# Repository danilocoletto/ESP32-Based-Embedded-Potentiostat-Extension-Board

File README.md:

# ESP32-Based Real-Time Embedded Potentiostat Extension Board

> **⚠️ PROJECT STATUS: ONGOING**
> This project is currently under active development. The hardware design and firmware are subject to changes. Please check the `dev` branch for the latest updates.

## Key Features

- Real-time embedded architecture using **ESP32 + FreeRTOS**
- **24-bit precision ADC (ADS1255)** for nanoampere current measurements
- **16-bit DAC waveform generation** for electrochemical techniques
- Modular **analog front-end (AFE)** design
- Designed for **voltammetry and amperometry**
- **KiCad open hardware design**
- Firmware based on **ESP-IDF**

## 📖 Introduction

This repository contains the open-source hardware and firmware for a **Real-Time Embedded Potentiostat**. Designed as a high-precision **modular extension board**, this instrument allows for advanced electrochemical analysis (Voltammetry, Amperometry) in field applications.

A defining feature of this design is its **controller-agnostic modularity**. The board functions as a dedicated analog "backpack," decoupling the sensitive electrochemical front-end from the digital control logic. This architecture allows the board to be driven by various devices depending on the application needs:

* **ESP32 Implementation (Current Focus):** The primary implementation utilizes an **ESP32** microcontroller. This was chosen to provide **hard real-time execution** via FreeRTOS and to enable **wireless connectivity** (Wi-Fi/Bluetooth) for remote field monitoring in the future development.
* **External Instrumentation:** The header layout and signal routing were specifically designed to allow direct interfacing with test equipment such as the **Analog Discovery 2** (or similar oscilloscopes/logic analyzers). This allows user flexibility to to have alternative control strategies such as an ESP32, ATMEGA, STM32 or even an Analog Discovery.

### 💡 The Evolution: From Single-Board Computer to Real-Time Embedded
This project represents the **second generation** of the "All-in-One" potentiostat concept.

* **Previous Design (Generation 1):** Based on a **Raspberry Pi 3B+**. While it successfully integrated the user interface and control logic, the reliance on a non-real-time Operating System (Linux) introduced latency challenges for high-speed techniques. The usage of the ADS1110 (240 SPS) also limited the sweep speed.
* **Current Design (Generation 2):** Transitions to an **Embedded Real-Time Architecture**.
    * **Why?** To achieve **deterministic timing** and modular flexibility.
    * **Improvements:** Modular hardware design suitable for extension, significantly lower power consumption, reduced noise floor (nanoampere-level), and the ability to perform fast electrochemical screening without a heavy OS overhead.

## 🛠️ Hardware & Components

The hardware is designed to support nanoampere-level current measurements with a robust analog front-end.
- **KiCad PCB design**
- **MCU:** **ESP32-WROOM/WROVER** (Dual-core, 240 MHz). Handles waveform generation (DAC control), data acquisition (ADC readings), and wireless communication.
- **Analog Front-End (TIA + Control Amplifier):**
    - Improved topology using **High-Precision Rail-to-Rail OpAmps** (e.g., LMP770x Series and LM7721) for the Transimpedance Amplifier (TIA) and Control Amplifier.
    - **MAX4737:** Low-voltage, low on-resistance (RON), quad single-pole/single throw (SPST) analog switches.
    - **MAX4617:** High-Speed, Low-Voltage, CMOS Analog Multiplexers/Switches
- **ADS1255**: 24-bit ADC High-Speed ADC (replacing the slower ADS1110 of the previous version for an ADS1255) to support faster sweep rates (>1000 mV/s) and filter line noise at low current measurements.
- **MAX5217**: 16-bit DAC Low-Power with I2C/SPI interface for precise potential steps.
- **Power Management:** On-board LDOs and precision voltage references (2.500V / 5.000V) to ensure stable operation in field conditions.
- **Anti-Aliasing:** Active 4th-order Sallen-Key filtering to smooth signal steps and reduce noise.

## Firmware

- **ESP-IDF framework**
- **FreeRTOS tasks**
- **SPI driver for ADS1255**
- **I2C driver for DAC**
- **State machine for system management**
- **Baremetal libraries for precise timing during experiments**

## 📂 Repository Structure

The repository is organized as follows:

```
├── Diseno_3D/                          # Fusion360 project and .stl files for 3D case design
├── Hardware/                           # KiCad project files (Schematics, PCB Layout, BOM)
├── Images&Schematics/
│   ├── Images/
│   ├── Interface/
│   ├── Renders/
│   ├── Schematics/
├── Software/ 
│   ├── ESP32_Firmware/ 
│   │   ├── PotentiostatV2_Firmware/    # ESP-IDF C/C++ source code
│   │   │   ├── main/                   # Core logic (FreeRTOS tasks, State Machine)
│   │   │   ├── components/             # Drivers for DAC, ADC, and Potentiostat control
│   │   ├── Main/                       # GUI and Python Backend modules
│   │   │   ├── modules/                # Python backend modules
│   │   │   ├── logos/                  # logos folder
│   │   │   ├── gui/                    # Graphic User Interface .ui file
├── Información/                        # Datasheets and design notes
└── README.md                           # This file
```

## 🔌 Pinout & Interface

*> **Note:** As the PCB layout is being finalized, please refer to the schematic in the `Hardware` folder for the most up-to-date netlist. Below is the current configuration for the ESP32 implementation.*

### ⚡ Analog Front-End Connections
* **WE (Working Electrode):** Input for current measurement.
* **RE (Reference Electrode):** Feedback input (Shielded).
* **CE (Counter Electrode):** Current injection output.

### 🧩 ESP32 GPIO Mapping

| Component | Function | ESP32 GPIO | Description |
| :--- | :--- | :--- | :--- |
| **ADS1255 (ADC)** | **MISO** (DOUT) | **19** | SPI Data Input |
| | **MOSI** (DIN) | **23** | SPI Data Output |
| | **SCLK** | **18** | SPI Clock |
| | **CS** | **5** | Chip Select |
| | **DRDY** | **4** | Data Ready Interrupt |
| | **CLOCK** | **16** | (Optional) ADS1255 System Clock |
| **MAX5217 (DAC)** | **SDA** | **21** | I2C Data |
| | **SCL** | **22** | I2C Clock |
| | **NAUX** | **32** | Aux/Load Control |
| **MAX4617 (Mux)** | **SEL A** | **27** | Range/Gain Select Bit A |
| | **SEL B** | **26** | Range/Gain Select Bit B |
| | **SEL C** | **25** | Range/Gain Select Bit C |
| **MAX4737 (Switches)**| **CR SHORT EN**| **14** | Counter-Reference Short Enable |
| | **RE FB EN** | **33** | Reference Feedback Enable |
| | **WE EN** | **13** | Working Electrode Enable |
| | **CE EN** | **15** | Counter Electrode Enable |
| **Misc** | **GREEN LED** | **2** | Onboard Status LED (Green) |

## 📚 References & Context

For context on the theoretical background and the first generation of this device, please refer to our published article on the Raspberry Pi-based version:

> **(All-in-One) Open Source Potentiostat for Field Analysis Based on Raspberry Pi**
> *Hardware* 2024, 3(4), 17; [https://doi.org/10.3390/hardware3040017](https://www.mdpi.com/2813-6640/3/4/17)

Case Design:

> *3D Printed Design by [Boris Diaduch](https://www.linkedin.com/in/borisdiaduch/)*

---

*Maintained by [Ing. Danilo Coletto Gallego](www.linkedin.com/in/danilocoletto)*

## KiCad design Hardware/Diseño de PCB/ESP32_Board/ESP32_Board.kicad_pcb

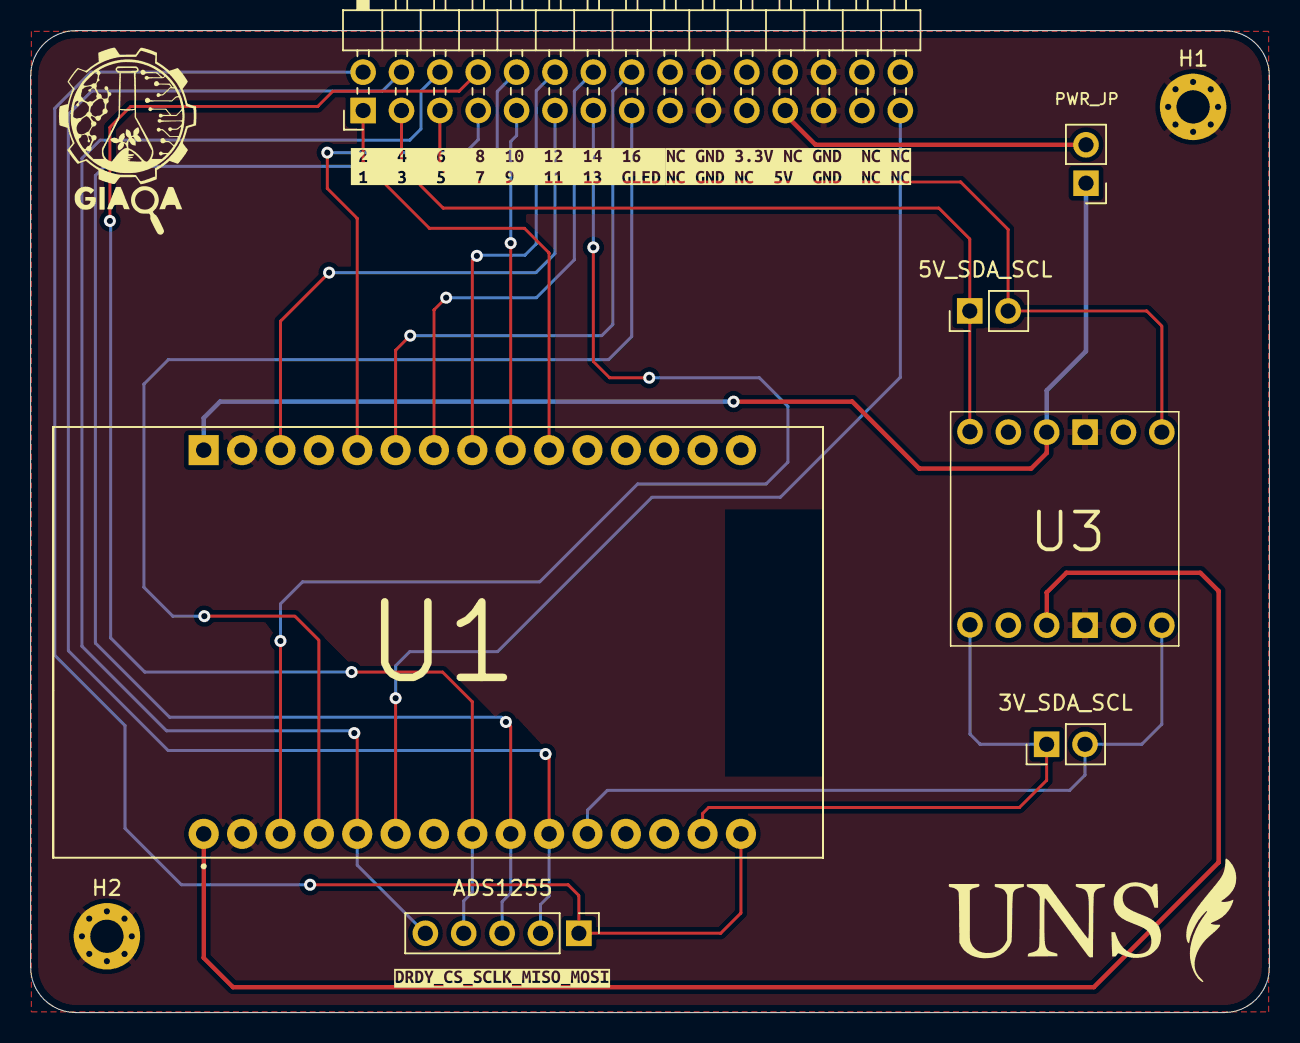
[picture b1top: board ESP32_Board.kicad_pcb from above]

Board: 2 copper layers, 82.0 x 65.0 mm, 13 parts (0 on the bottom side), 23 nets.

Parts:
3V_SDA_SCL, 5V_SDA_SCL: Conn_01x02; PinHeader_1x02_P2.54mm_Vertical
ADS1255: Conn_01x05; PinHeader_1x05_P2.54mm_Vertical
H1, H2: MountingHole_Pad; MountingHole_2.2mm_M2_Pad_Via
J1: Conn_02x15_Odd_Even; PinHeader_2x15_P2.54mm_Horizontal
PWR_JP: Jumper_2_Open; PinHeader_1x02_P2.54mm_Vertical
U1: ESP32 - DEVKIT; MODULE_ESP32_DEVKIT_V1_CORRECTED
U2: logo; logo_uns
U3: LevelShifter
kibuzzard-69A1DE73: G***; kibuzzard-69A1DE73
kibuzzard-69A5AE09: G***; kibuzzard-69A5AE09
kibuzzard-69C42740: G***; kibuzzard-69C42740

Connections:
+3.3V: U1.2 (3V3), U3.3 (3.3V)
+5V: PWR_JP.1 (A), U1.0 (VIN), U3.10 (5V)
/5V: J1.23, PWR_JP.2 (B)
/ADS1255_CLOCK_PIN: J1.29, U1.27 (RX2/D16)
/ADS1255_CS: ADS1255.4, J1.8, U1.29 (D5)
/ADS1255_DIN_MOSI: ADS1255.1, J1.2, U1.37 (D23)
/ADS1255_DOUT_MISO: ADS1255.2, J1.4, U1.31 (D19)
/ADS1255_DRDY: ADS1255.5, J1.6, U1.26 (D4)
/ADS1255_SCLK: ADS1255.3, J1.10, U1.30 (D18)
/GREEN_LED: J1.15, U1.24 (D2)
/MAX4617_SEL_A: J1.16, U1.12 (D27)
/MAX4617_SEL_B: J1.14, U1.11 (D26)
/MAX4617_SEL_C: J1.12, U1.10 (D25)
/MAX4737_CE_EN: J1.13, U1.23 (D15)
/MAX4737_CR_SHORT_EN: J1.7, U1.13 (D14)
/MAX4737_RE_FB_EN: J1.9, U1.9 (D33)
/MAX4737_WE_EN: J1.11, U1.16 (D13)
/MAX_5217_NAUX: J1.1, U1.8 (D32)
/MAX_5217_SCL: 3V_SDA_SCL.1, U1.36 (D22), U3.1 (TXI1)
/MAX_5217_SDA: 3V_SDA_SCL.2, U1.33 (D21), U3.6 (TXI2)
/TO_DAC_SCL_PIN_3: 5V_SDA_SCL.1, J1.3, U3.12 (TXD1)
/TO_DAC_SDA_PIN_5: 5V_SDA_SCL.2, J1.5, U3.7 (TXD2)
GND: H1.1, H2.1, J1.19, J1.20, J1.25, J1.26, U1.1 (GND), U1.38 (GND), U3.4 (GND), U3.9 (GND)

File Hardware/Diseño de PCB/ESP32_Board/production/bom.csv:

Designator,Footprint,Quantity,Value,LCSC Part #
"3V_SDA_SCL, 5V_SDA_SCL",PinHeader_1x02_P2.54mm_Vertical,2,Conn_01x02,
ADS1255,PinHeader_1x05_P2.54mm_Vertical,1,Conn_01x05,
J1,PinHeader_2x15_P2.54mm_Horizontal,1,Conn_02x15_Odd_Even,
PWR_JP,PinHeader_1x02_P2.54mm_Vertical,1,Jumper_2_Open,
U1,MODULE_ESP32_DEVKIT_V1_CORRECTED,1,ESP32 - DEVKIT,
U3,LevelShifter,1,~,

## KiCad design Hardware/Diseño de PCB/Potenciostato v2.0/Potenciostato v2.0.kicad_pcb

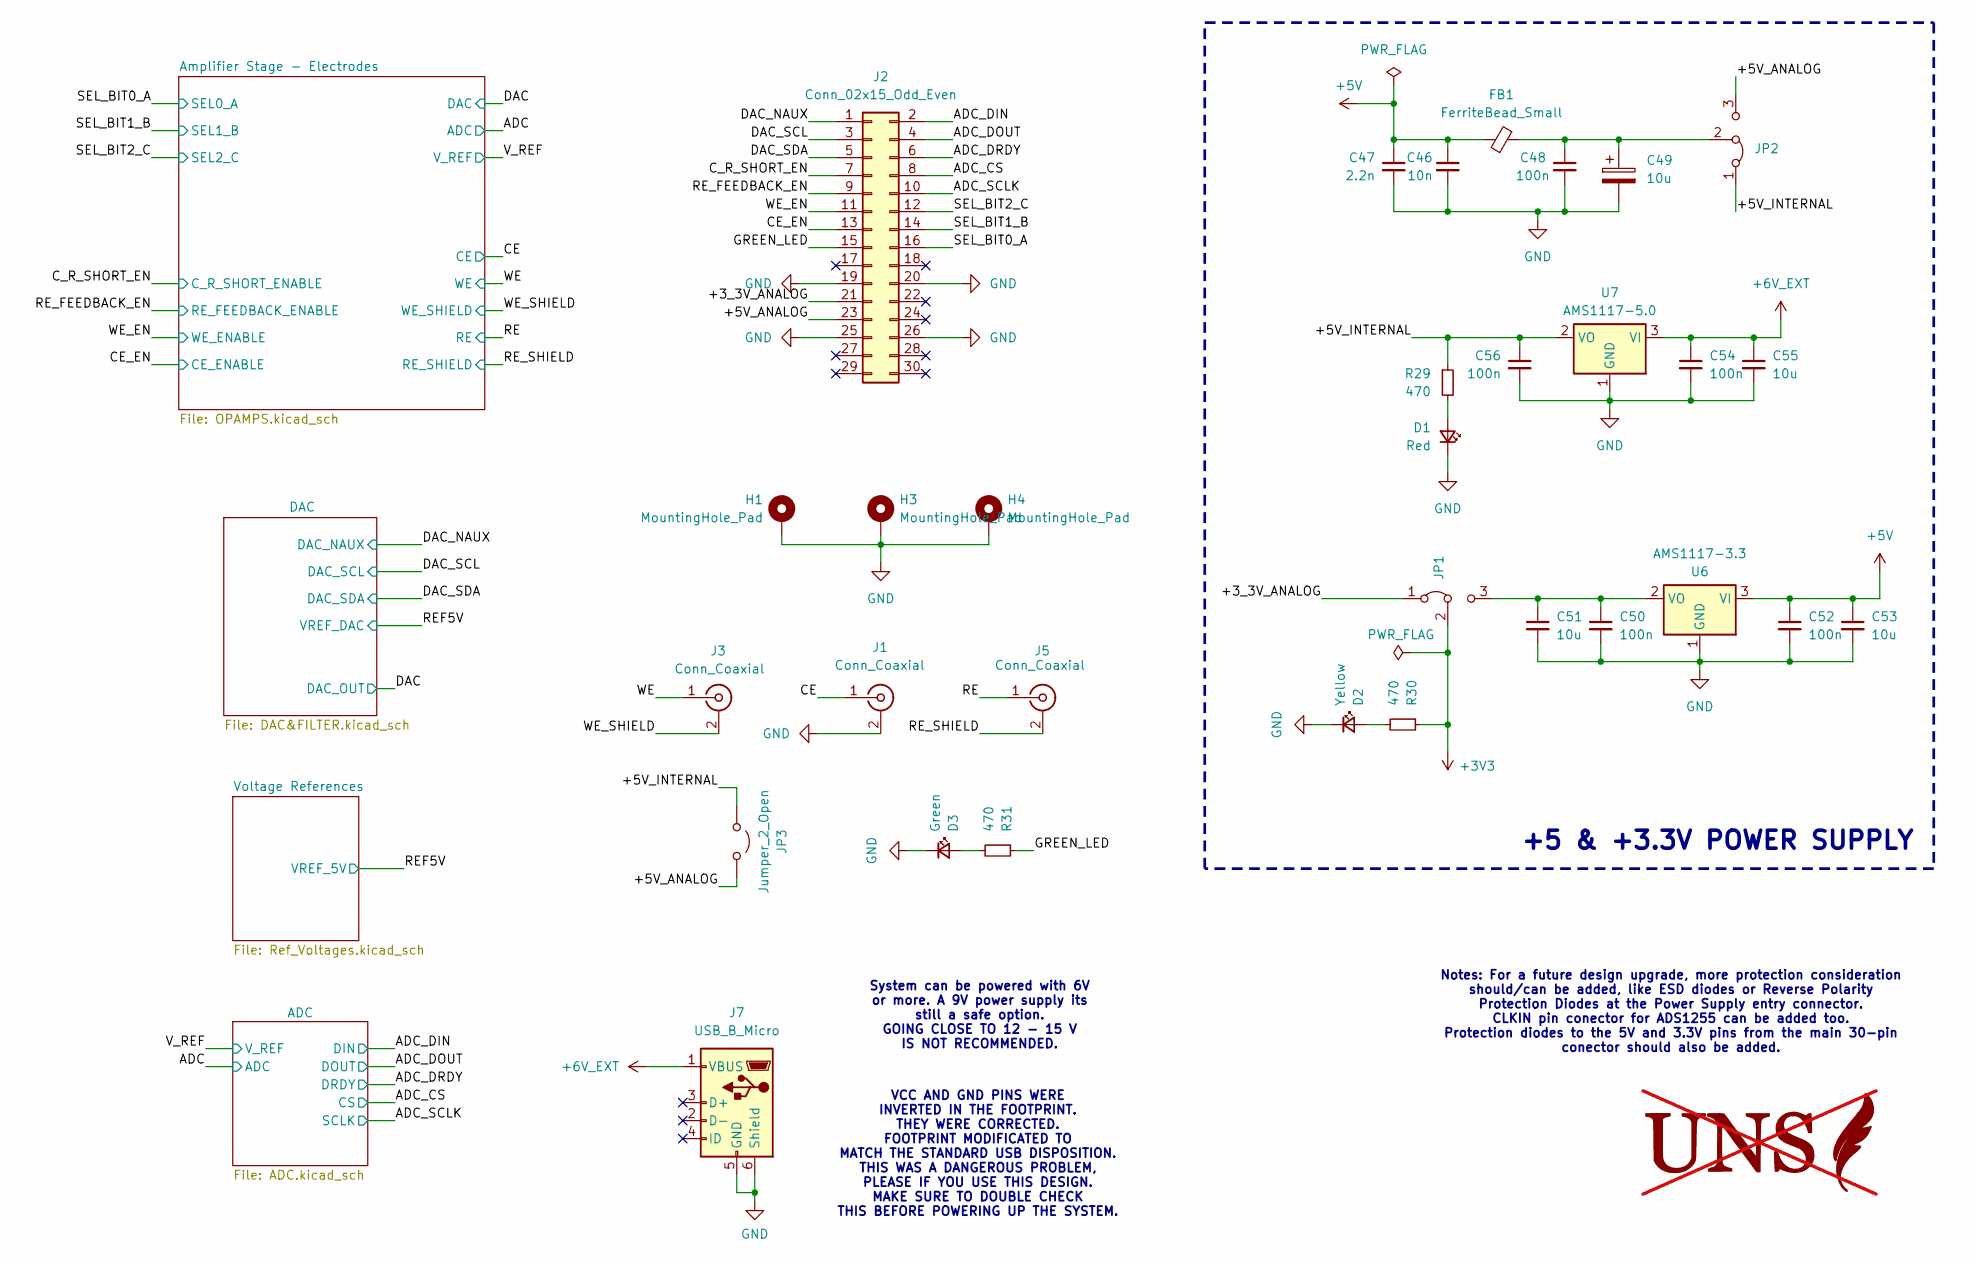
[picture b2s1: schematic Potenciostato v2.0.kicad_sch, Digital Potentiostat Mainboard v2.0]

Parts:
C46: 10n; C_0805_2012Metric_Pad1.18x1.45mm_HandSolder
C47: 2.2n; C_1206_3216Metric_Pad1.33x1.80mm_HandSolder
C48, C50, C52, C54, C56: 100n; C_0805_2012Metric_Pad1.18x1.45mm_HandSolder
C49: 10u; CP_Elec_4x5.4
C51, C53, C55: 10u; CP_EIA-6032-20_AVX-F_Pad2.25x2.35mm_HandSolder
D1: Red; LED_1206_3216Metric_Pad1.42x1.75mm_HandSolder
D2: Yellow; LED_1206_3216Metric_Pad1.42x1.75mm_HandSolder
D3: Green; LED_1206_3216Metric_Pad1.42x1.75mm_HandSolder
FB1: FerriteBead_Small; L_0603_1608Metric_Pad1.05x0.95mm_HandSolder; MFR.Part # PZ1608D102-R80TF; JLCPCB Part # C279752
H1, H3, H4: MountingHole_Pad; MountingHole_2.2mm_M2_Pad_Via
J1, J3, J5: Conn_Coaxial; BNC_Amphenol_B6252HB-NPP3G-50_Horizontal
J2: Conn_02x15_Odd_Even; PinSocket_2x15_P2.54mm_Horizontal
J7: USB_B_Micro; USB_Micro-B_GCT_USB3076-30-A
JP1, JP2: Jumper_3_Bridged12; PinHeader_1x03_P2.54mm_Vertical
JP3: Jumper_2_Open; TestPoint_2Pads_Pitch2.54mm_Drill0.8mm
R29, R30, R31: 470; R_0603_1608Metric_Pad0.98x0.95mm_HandSolder
U6: AMS1117-3.3; SOT-223-3_TabPin2
U7: AMS1117-5.0; SOT-223-3_TabPin2
U8: not fitted

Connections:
+3V3: JP1.2 (C), R30.1; also elsewhere on the board
+5V: C46.1, C47.1, C52.1, C53.1, FB1.1, U6.3 (VI); also elsewhere on the board
+6V_EXT: C54.1, C55.1, J7.1 (VBUS), U7.3 (VI); also elsewhere on the board
/+3_3V_ANALOG: J2.21, JP1.1 (A)
/+5V_ANALOG: J2.23, JP2.3 (B), JP3.2 (B)
/+5V_INTERNAL: C56.1, JP2.1 (A), JP3.1 (A), R29.1, U7.2 (VO)
/ADC_CS: J2.8; also elsewhere on the board
/ADC_DIN: J2.2; also elsewhere on the board
/ADC_DOUT: J2.4; also elsewhere on the board
/ADC_DRDY: J2.6; also elsewhere on the board
/ADC_SCLK: J2.10; also elsewhere on the board
/CE: J1.1 (In); also elsewhere on the board
/CE_EN: J2.13; also elsewhere on the board
/C_R_SHORT_EN: J2.7; also elsewhere on the board
/DAC_NAUX: J2.1; also elsewhere on the board
/DAC_SCL: J2.3; also elsewhere on the board
/DAC_SDA: J2.5; also elsewhere on the board
/GREEN_LED: J2.15, R31.1
/RE: J5.1 (In); also elsewhere on the board
/RE_FEEDBACK_EN: J2.9; also elsewhere on the board
/RE_SHIELD: J5.2 (Ext); also elsewhere on the board
/SEL_BIT0: J2.16; also elsewhere on the board
/SEL_BIT1: J2.14; also elsewhere on the board
/SEL_BIT2: J2.12; also elsewhere on the board
/WE: J3.1 (In); also elsewhere on the board
/WE_EN: J2.11; also elsewhere on the board
/WE_SHIELD: J3.2 (Ext); also elsewhere on the board
GND: C46.2, C47.2, C48.2, C49.2, C50.2, C51.2, C52.2, C53.2, C54.2, C55.2, C56.2, D1.1 (K), D2.1 (K), D3.1 (K), H1.1, H3.1, H4.1, J1.2 (Ext), J2.19, J2.20, J2.25, J2.26, J7.5 (GND), J7.6 (Shield), U6.1 (GND), U7.1 (GND); also elsewhere on the board
unnamed: D1.2 (A), R29.2
unnamed: D2.2 (A), R30.2
unnamed: D3.2 (A), R31.2
unnamed: C50.1, C51.1, JP1.3 (B), U6.2 (VO)
unnamed: C48.1, C49.1, FB1.2, JP2.2 (C)

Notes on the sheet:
+5 & +3.3V POWER SUPPLY
Notes: For a future design upgrade, more protection consideration should/can be added, like ESD diodes or Reverse Polarity Protection Diodes at the Power Supply entry connector. CLKIN pin conector for ADS1255 can be added too. Protection diodes to the 5V and 3.3V pins from the main 30-pin conector 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
VCC AND GND PINS WERE INVERTED IN THE FOOTPRINT. THEY WERE CORRECTED. FOOTPRINT MODIFICATED TO MATCH THE STANDARD USB DISPOSITION. THIS WAS A DANGEROUS PROBLEM, PLEASE IF YOU USE THIS DESIGN. MAKE SURE TO DOUBLE CHECK THIS BEFORE POWERING UP THE SYSTEM.
System can be powered with 6V or more. A 9V power supply its still a safe option. GOING CLOSE TO 12 - 15 V IS NOT RECOMMENDED.

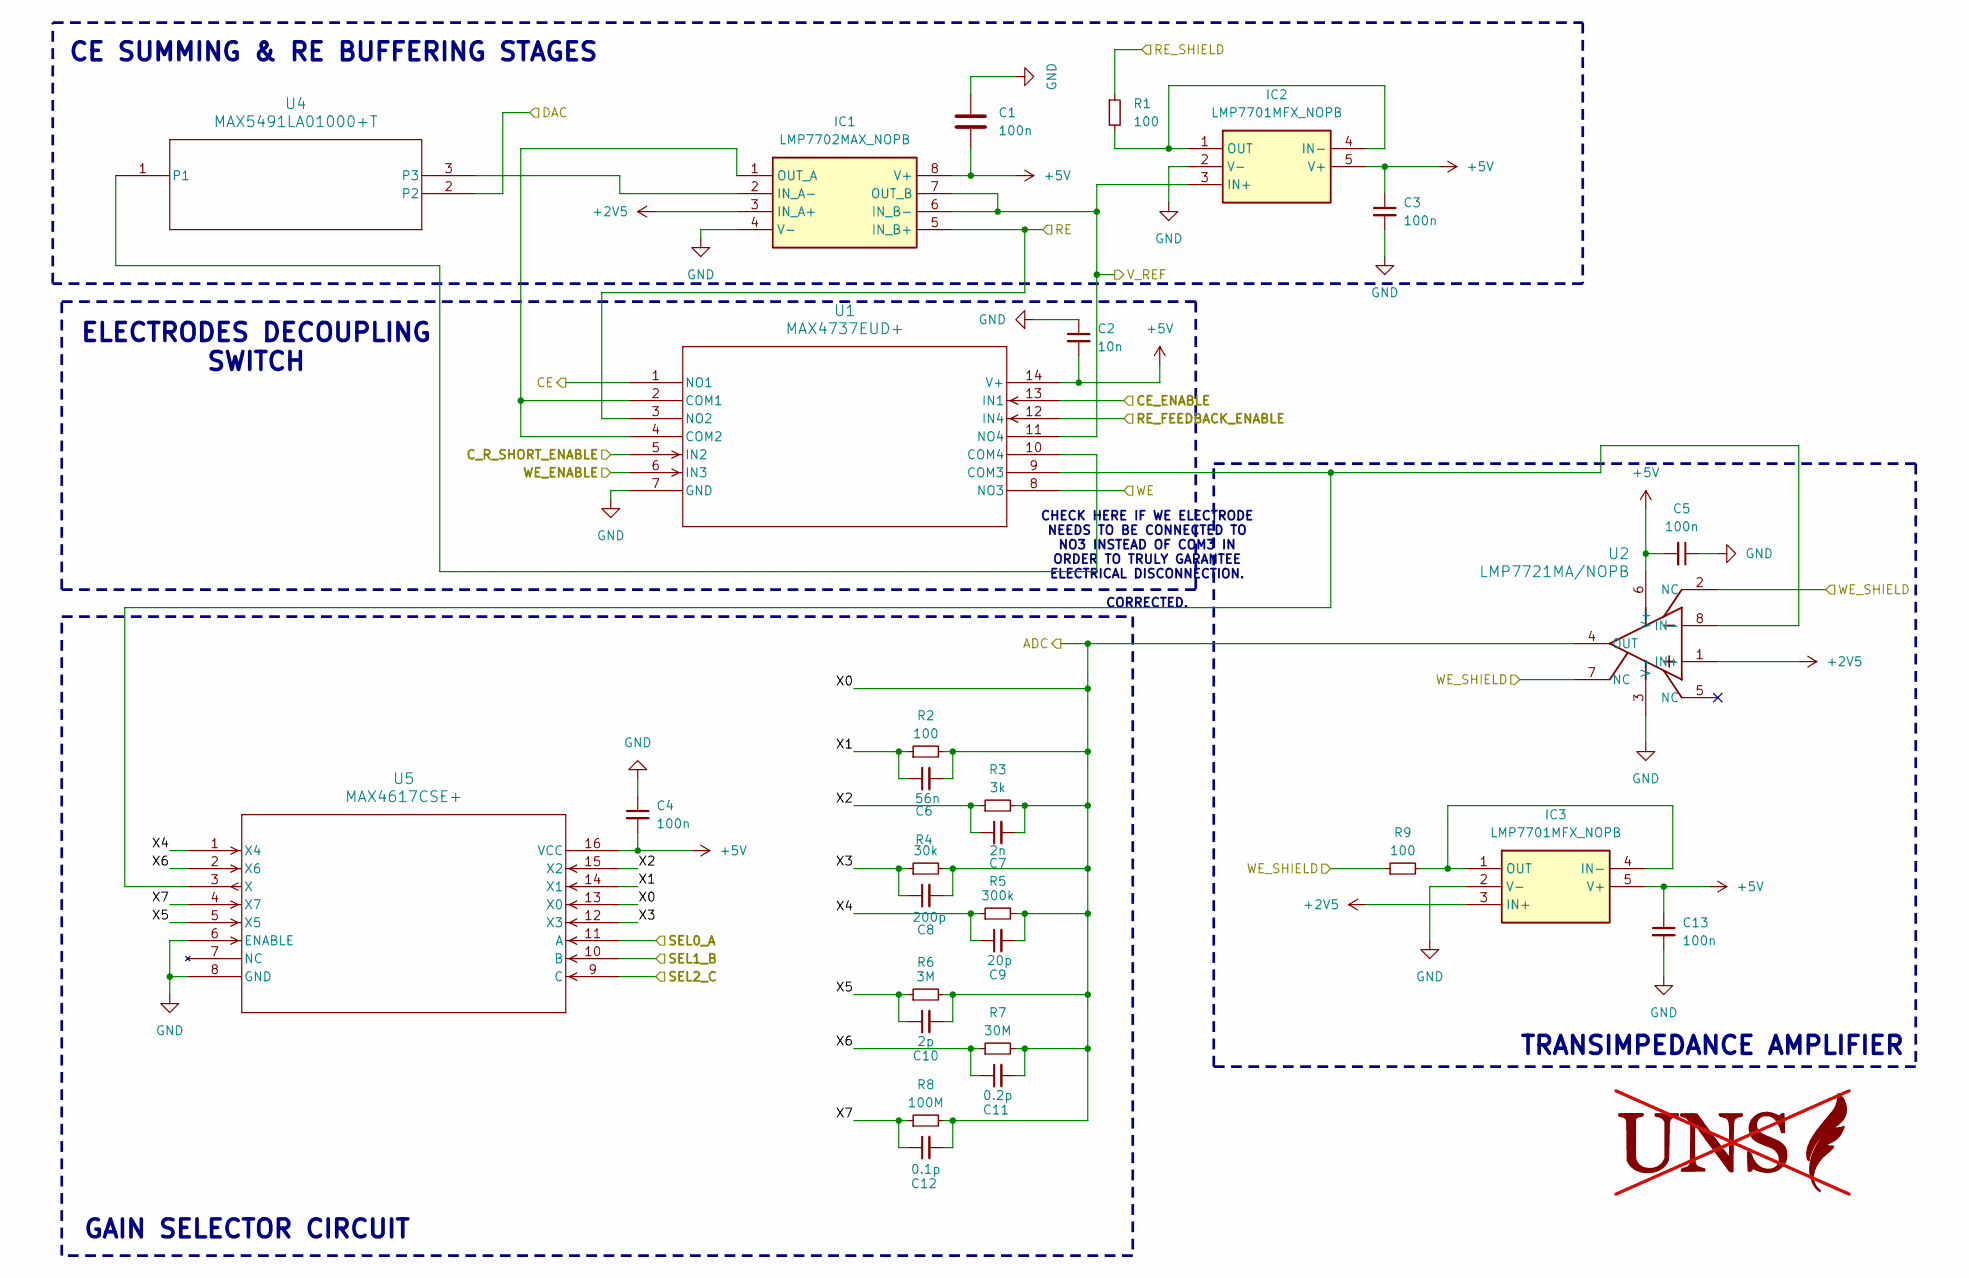
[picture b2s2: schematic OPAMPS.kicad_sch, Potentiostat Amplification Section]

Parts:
C1, C3, C4, C5, C13: 100n; C_0805_2012Metric_Pad1.18x1.45mm_HandSolder
C2: 10n; C_0805_2012Metric_Pad1.18x1.45mm_HandSolder
C6: 56n; C_0805_2012Metric_Pad1.18x1.45mm_HandSolder
C7: 2n; C_0805_2012Metric_Pad1.18x1.45mm_HandSolder
C8: 200p; C_0805_2012Metric_Pad1.18x1.45mm_HandSolder
C9: 20p; C_0805_2012Metric_Pad1.18x1.45mm_HandSolder
C10: 2p; C_0805_2012Metric_Pad1.18x1.45mm_HandSolder
C11: 0.2p; C_0805_2012Metric_Pad1.18x1.45mm_HandSolder
C12: 0.1p; C_0805_2012Metric_Pad1.18x1.45mm_HandSolder
IC1: LMP7702MAX_NOPB; SOIC127P600X175_LMP7702; MFR.Part # LMP7702MAX/NOPB
IC2, IC3: LMP7701MFX_NOPB; SOT95P280X145_LMP7701; MFR.Part # LMP7701MFX/NOPB
R1, R2, R9: 100; R_0805_2012Metric_Pad1.20x1.40mm_HandSolder
R3: 3k; R_0805_2012Metric_Pad1.20x1.40mm_HandSolder
R4: 30k; R_0805_2012Metric_Pad1.20x1.40mm_HandSolder
R5: 300k; R_0805_2012Metric_Pad1.20x1.40mm_HandSolder
R6: 3M; R_0805_2012Metric_Pad1.20x1.40mm_HandSolder
R7: 30M; R_0805_2012Metric_Pad1.20x1.40mm_HandSolder
R8: 100M; R_0805_2012Metric_Pad1.20x1.40mm_HandSolder
U1: MAX4737EUD+; MAX4737
U2: LMP7721MA/NOPB; M08ALMP7721_
U4: MAX5491LA01000+T; SOT23_5491
U5: MAX4617CSE+; MAX4617
U9: not fitted

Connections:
+2V5: IC1.3 (IN_A+), IC3.3 (IN+), U2.1 (IN+); also elsewhere on the board
+5V: C1.2, C2.2, C3.1, C4.2, C5.2, C13.1, IC1.8 (V+), IC2.5 (V+), IC3.5 (V+), U1.14 (V+), U2.6 (V+), U5.16 (VCC); also elsewhere on the board
/ADC: C6.2, C7.2, C8.2, C9.2, C10.2, C11.2, C12.2, R2.2, R3.2, R4.2, R5.2, R6.2, R7.2, R8.2, U2.4 (OUT), U5.13 (X0); also elsewhere on the board
/Amplifier Stage - Electrodes/X1: C6.1, R2.1, U5.14 (X1)
/Amplifier Stage - Electrodes/X2: C7.1, R3.1, U5.15 (X2)
/Amplifier Stage - Electrodes/X3: C8.1, R4.1, U5.12 (X3)
/Amplifier Stage - Electrodes/X4: C9.1, R5.1, U5.1 (X4)
/Amplifier Stage - Electrodes/X5: C10.1, R6.1, U5.5 (X5)
/Amplifier Stage - Electrodes/X6: C11.1, R7.1, U5.2 (X6)
/Amplifier Stage - Electrodes/X7: C12.1, R8.1, U5.4 (X7)
/CE: U1.1 (NO1); also elsewhere on the board
/CE_EN: U1.13 (IN1); also elsewhere on the board
/C_R_SHORT_EN: U1.5 (IN2); also elsewhere on the board
/DAC: U4.2; also elsewhere on the board
/RE: IC1.5 (IN_B+), U1.3 (NO2); also elsewhere on the board
/RE_FEEDBACK_EN: U1.12 (IN4); also elsewhere on the board
/RE_SHIELD: R1.1; also elsewhere on the board
/SEL_BIT0: U5.11 (A); also elsewhere on the board
/SEL_BIT1: U5.10 (B); also elsewhere on the board
/SEL_BIT2: U5.9 (C); also elsewhere on the board
/V_REF: IC1.6 (IN_B-), IC1.7 (OUT_B), IC2.3 (IN+), U1.11 (NO4); also elsewhere on the board
/WE: U1.8 (NO3); also elsewhere on the board
/WE_EN: U1.6 (IN3); also elsewhere on the board
/WE_SHIELD: R9.1, U2.2 (NC), U2.7 (NC); also elsewhere on the board
GND: C1.1, C2.1, C3.2, C4.1, C5.1, C13.2, IC1.4 (V-), IC2.2 (V-), IC3.2 (V-), U1.7 (GND), U2.3 (V-), U5.6 (ENABLE), U5.8 (GND); also elsewhere on the board
unnamed: IC1.2 (IN_A-), U4.3
unnamed: IC1.1 (OUT_A), U1.2 (COM1), U1.4 (COM2)
unnamed: IC2.1 (OUT), IC2.4 (IN-), R1.2
unnamed: IC3.1 (OUT), IC3.4 (IN-), R9.2
unnamed: U1.10 (COM4), U4.1
unnamed: U1.9 (COM3), U2.8 (IN-), U5.3 (X)

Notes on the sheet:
GAIN SELECTOR CIRCUIT
CE SUMMING & RE BUFFERING STAGES
CHECK HERE IF WE ELECTRODE NEEDS TO BE CONNECTED TO NO3 INSTEAD OF COM3 IN ORDER TO TRULY GARANTEE ELECTRICAL DISCONNECTION. CORRECTED.
TRANSIMPEDANCE AMPLIFIER
ELECTRODES DECOUPLING SWITCH

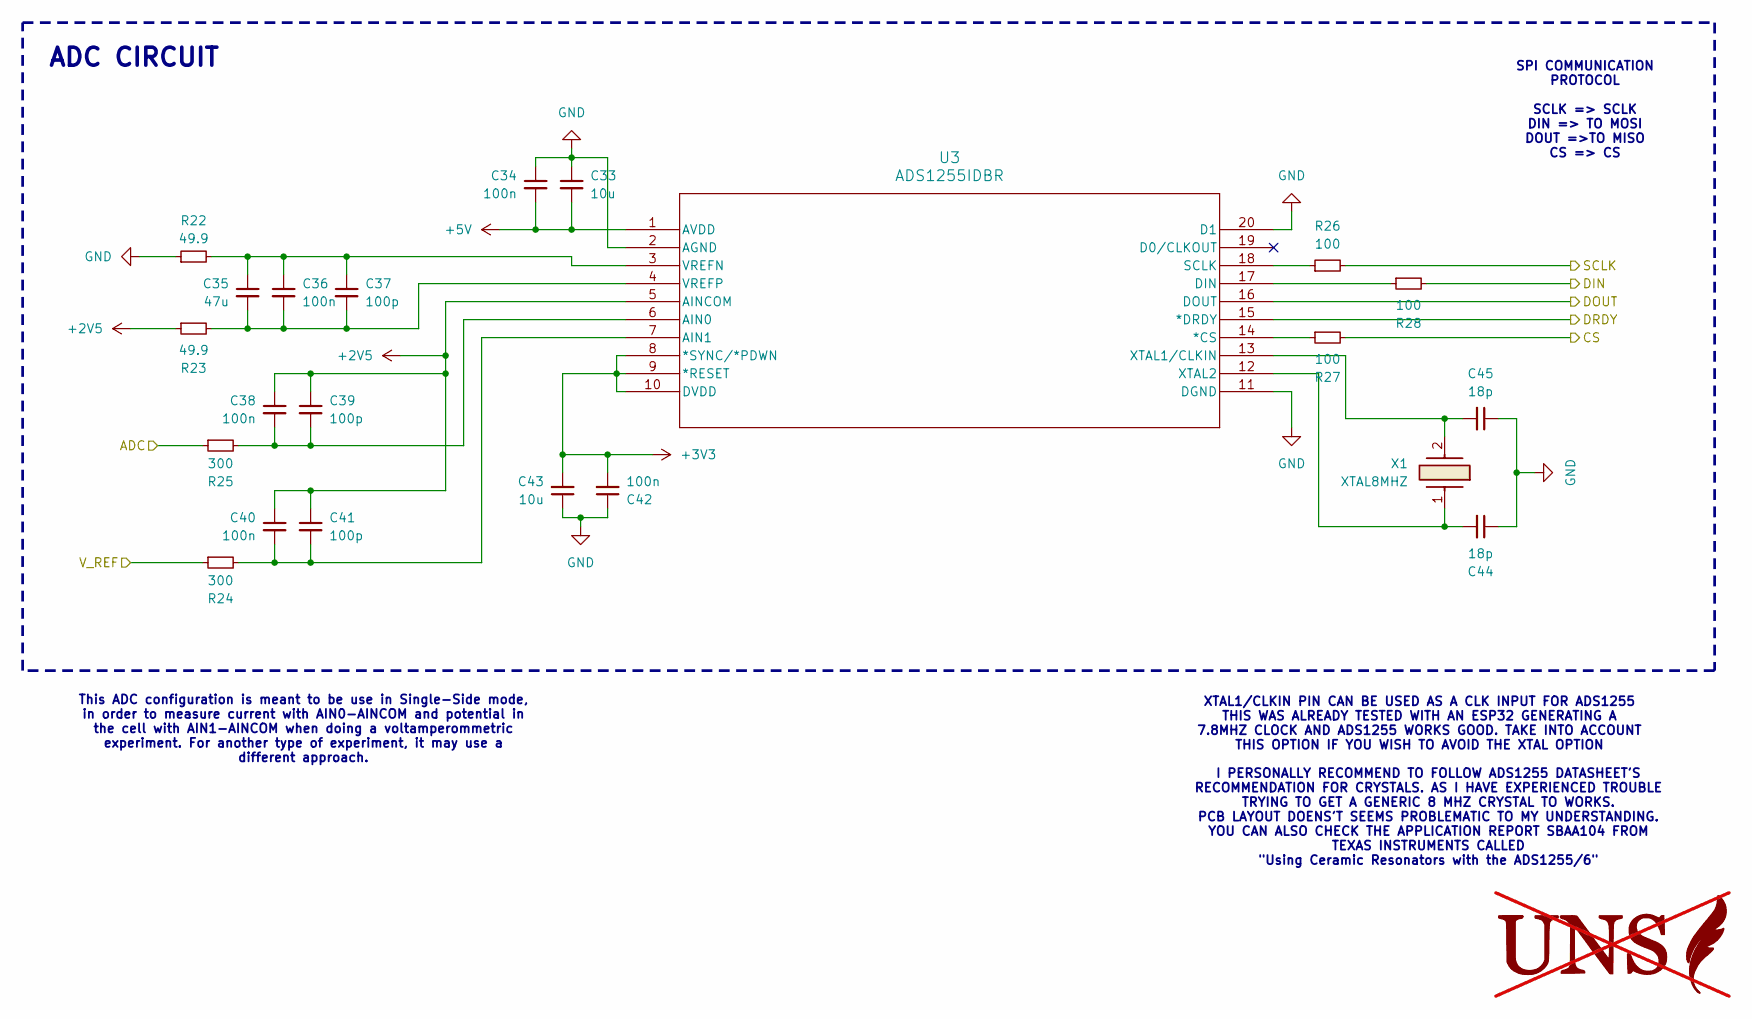
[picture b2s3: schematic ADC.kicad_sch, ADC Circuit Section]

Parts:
C33, C43: 10u; C_0805_2012Metric_Pad1.18x1.45mm_HandSolder
C34, C36, C38, C40, C42: 100n; C_0805_2012Metric_Pad1.18x1.45mm_HandSolder
C35: 47u; C_0805_2012Metric_Pad1.18x1.45mm_HandSolder
C37, C39, C41: 100p; C_0805_2012Metric_Pad1.18x1.45mm_HandSolder
C44, C45: 18p; C_0805_2012Metric_Pad1.18x1.45mm_HandSolder
R22, R23: 49.9; R_0805_2012Metric_Pad1.20x1.40mm_HandSolder
R24, R25: 300; R_0603_1608Metric_Pad0.98x0.95mm_HandSolder
R26, R27, R28: 100; R_0805_2012Metric_Pad1.20x1.40mm_HandSolder
U3: ADS1255IDBR; DB20_ADS1255
U12: not fitted
X1: XTAL8MHZ; CRYSTAL_8; MFR.Part # ECS-80-18-30Q-VY-TR

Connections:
+2V5: C38.1, C39.1, C40.1, C41.1, R23.1, U3.5 (AINCOM); also elsewhere on the board
+3V3: C42.2, C43.2, U3.8 (*SYNC/*PDWN), U3.9 (*RESET), U3.10 (DVDD); also elsewhere on the board
+5V: C33.2, C34.2, U3.1 (AVDD); also elsewhere on the board
/ADC: R25.1; also elsewhere on the board
/ADC_CS: R27.2; also elsewhere on the board
/ADC_DIN: R28.2; also elsewhere on the board
/ADC_DOUT: U3.16 (DOUT); also elsewhere on the board
/ADC_DRDY: U3.15 (*DRDY); also elsewhere on the board
/ADC_SCLK: R26.2; also elsewhere on the board
/V_REF: R24.1; also elsewhere on the board
GND: C33.1, C34.1, C42.1, C43.1, C44.1, C45.1, R22.1, U3.2 (AGND), U3.11 (DGND), U3.20 (D1); also elsewhere on the board
unnamed: R27.1, U3.14 (*CS)
unnamed: C38.2, C39.2, R25.2, U3.6 (AIN0)
unnamed: C40.2, C41.2, R24.2, U3.7 (AIN1)
unnamed: R28.1, U3.17 (DIN)
unnamed: R26.1, U3.18 (SCLK)
unnamed: C35.1, C36.1, C37.1, R22.2, U3.3 (VREFN)
unnamed: C35.2, C36.2, C37.2, R23.2, U3.4 (VREFP)
unnamed: C45.2, U3.13 (XTAL1/CLKIN), X1.2
unnamed: C44.2, U3.12 (XTAL2), X1.1

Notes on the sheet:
SPI COMMUNICATION PROTOCOL SCLK => SCLK DIN => TO MOSI DOUT =>TO MISO CS => CS
This ADC configuration is meant to be use in Single-Side mode, in order to measure current with AIN0-AINCOM and potential in the cell with AIN1-AINCOM when doing a voltamperommetric experiment. For another type of experiment, it may use a different approach.
XTAL1/CLKIN PIN CAN BE USED AS A CLK INPUT FOR ADS1255 THIS WAS ALREADY TESTED WITH AN ESP32 GENERATING A 7.8MHZ CLOCK AND ADS1255 WORKS GOOD. TAKE INTO ACCOUNT THIS OPTION IF YOU WISH TO AVOID THE XTAL OPTION
I PERSONALLY RECOMMEND TO FOLLOW ADS1255 DATASHEET'S RECOMMENDATION FOR CRYSTALS. AS I HAVE EXPERIENCED TROUBLE TRYING TO GET A GENERIC 8 MHZ CRYSTAL TO WORKS. PCB LAYOUT DOENS'T SEEMS PROBLEMATIC TO MY UNDERSTANDING. YOU CAN ALSO CHECK THE APPLICATION REPORT SBAA104 FROM TEXAS INSTRUMENTS CALLED "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
ADC CIRCUIT

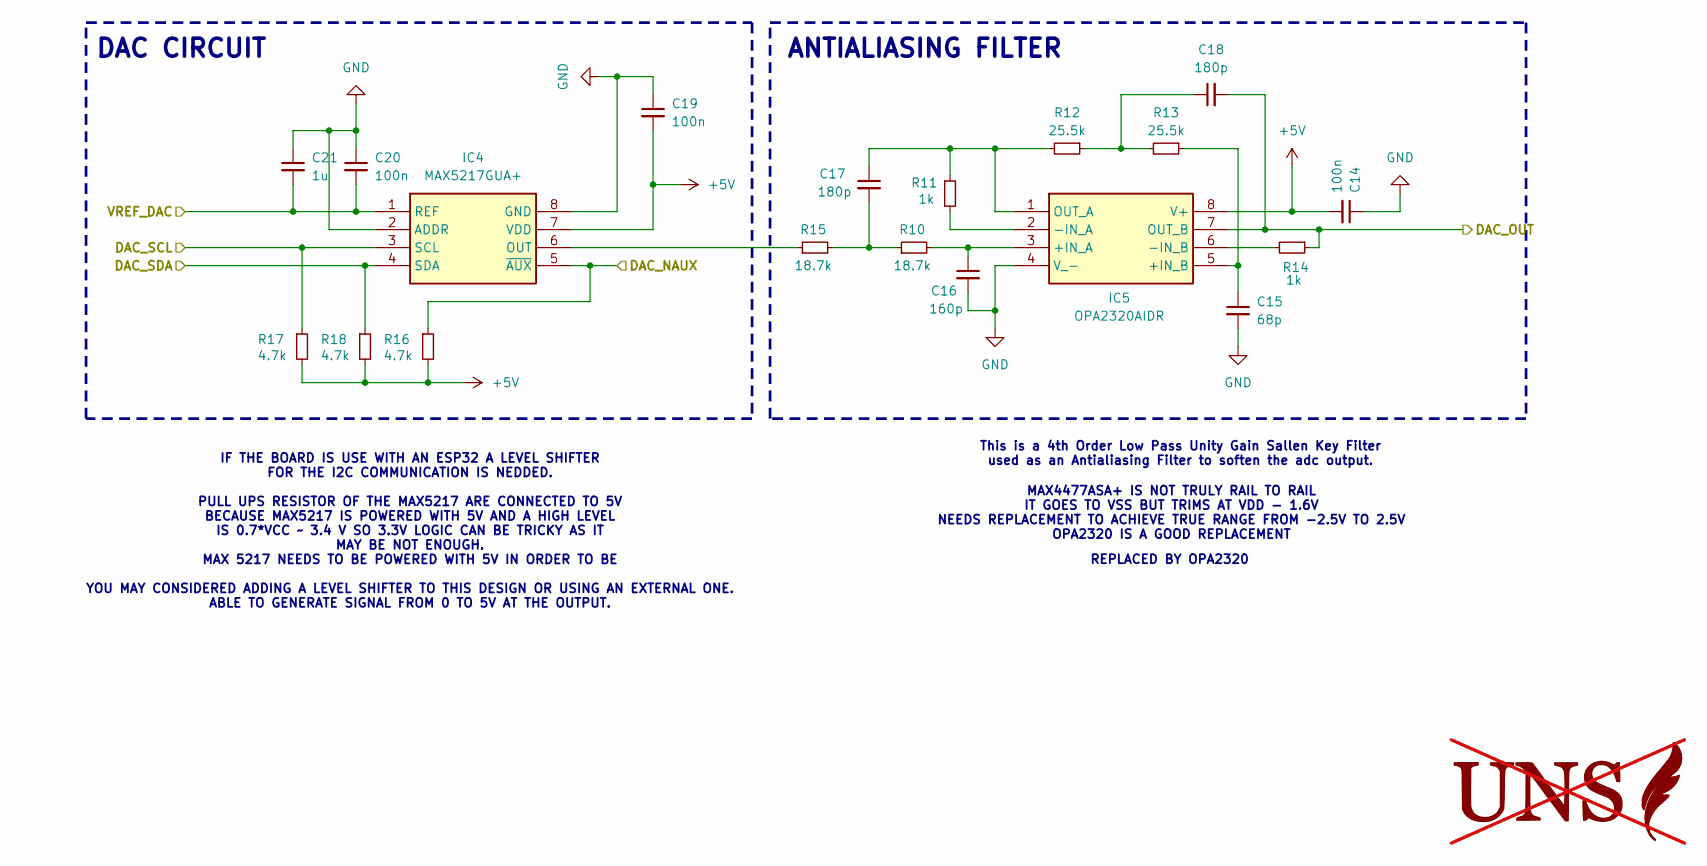
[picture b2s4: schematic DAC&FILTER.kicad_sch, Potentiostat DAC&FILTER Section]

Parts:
C14, C19, C20: 100n; C_0805_2012Metric_Pad1.18x1.45mm_HandSolder
C15: 68p; C_0805_2012Metric_Pad1.18x1.45mm_HandSolder
C16: 160p; C_0805_2012Metric_Pad1.18x1.45mm_HandSolder
C17, C18: 180p; C_0805_2012Metric_Pad1.18x1.45mm_HandSolder
C21: 1u; C_1206_3216Metric_Pad1.33x1.80mm_HandSolder
IC4: MAX5217GUA+; SOP65P490X110_MAX5217; MFR.Part # MAX5217GUA+
IC5: OPA2320AIDR; SOIC127P600X175-8N
R10, R15: 18.7k; R_0603_1608Metric_Pad0.98x0.95mm_HandSolder
R11, R14: 1k; R_0603_1608Metric_Pad0.98x0.95mm_HandSolder
R12, R13: 25.5k; R_0603_1608Metric_Pad0.98x0.95mm_HandSolder
R16, R17, R18: 4.7k; R_0603_1608Metric_Pad0.98x0.95mm_HandSolder
U10: not fitted

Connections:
+5V: C14.2, C19.2, IC4.7 (VDD), IC5.8 (V+), R16.2, R17.2, R18.2; also elsewhere on the board
/DAC: C18.2, IC5.7 (OUT_B), R14.1; also elsewhere on the board
/DAC_NAUX: IC4.5 (~AUX), R16.1; also elsewhere on the board
/DAC_SCL: IC4.3 (SCL), R17.1; also elsewhere on the board
/DAC_SDA: IC4.4 (SDA), R18.1; also elsewhere on the board
/REF5V: C20.2, C21.2, IC4.1 (REF); also elsewhere on the board
GND: C14.1, C15.2, C16.2, C19.1, C20.1, C21.1, IC4.2 (ADDR), IC4.8 (GND), IC5.4 (V_-); also elsewhere on the board
unnamed: C17.2, R10.1, R15.2
unnamed: C18.1, R12.1, R13.2
unnamed: IC4.6 (OUT), R15.1
unnamed: C16.1, IC5.3 (+IN_A), R10.2
unnamed: C15.1, IC5.5 (+IN_B), R13.1
unnamed: IC5.2 (-IN_A), R11.2
unnamed: IC5.6 (-IN_B), R14.2
unnamed: C17.1, IC5.1 (OUT_A), R11.1, R12.2

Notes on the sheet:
IF THE BOARD IS USE WITH AN ESP32 A LEVEL SHIFTER FOR THE I2C COMMUNICATION IS NEDDED. PULL UPS RESISTOR OF THE MAX5217 ARE CONNECTED TO 5V BECAUSE MAX5217 IS POWERED WITH 5V AND A HIGH LEVEL IS 0.7*VCC ~ 3.4 V SO 3.3V LOGIC CAN BE TRICKY AS IT MAY BE NOT ENOUGH. MAX 5217 NEEDS TO BE POWERED WITH 5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
ANTIALIASING FILTER
REPLACED BY OPA2320
MAX4477ASA+ IS NOT TRULY RAIL TO RAIL IT GOES TO VSS BUT TRIMS AT VDD - 1.6V NEEDS REPLACEMENT TO ACHIEVE TRUE RANGE FROM -2.5V TO 2.5V OPA2320 IS A GOOD REPLACEMENT
This is a 4th Order Low Pass Unity Gain Sallen Key Filter used as an Antialiasing Filter to soften the adc output.
DAC CIRCUIT

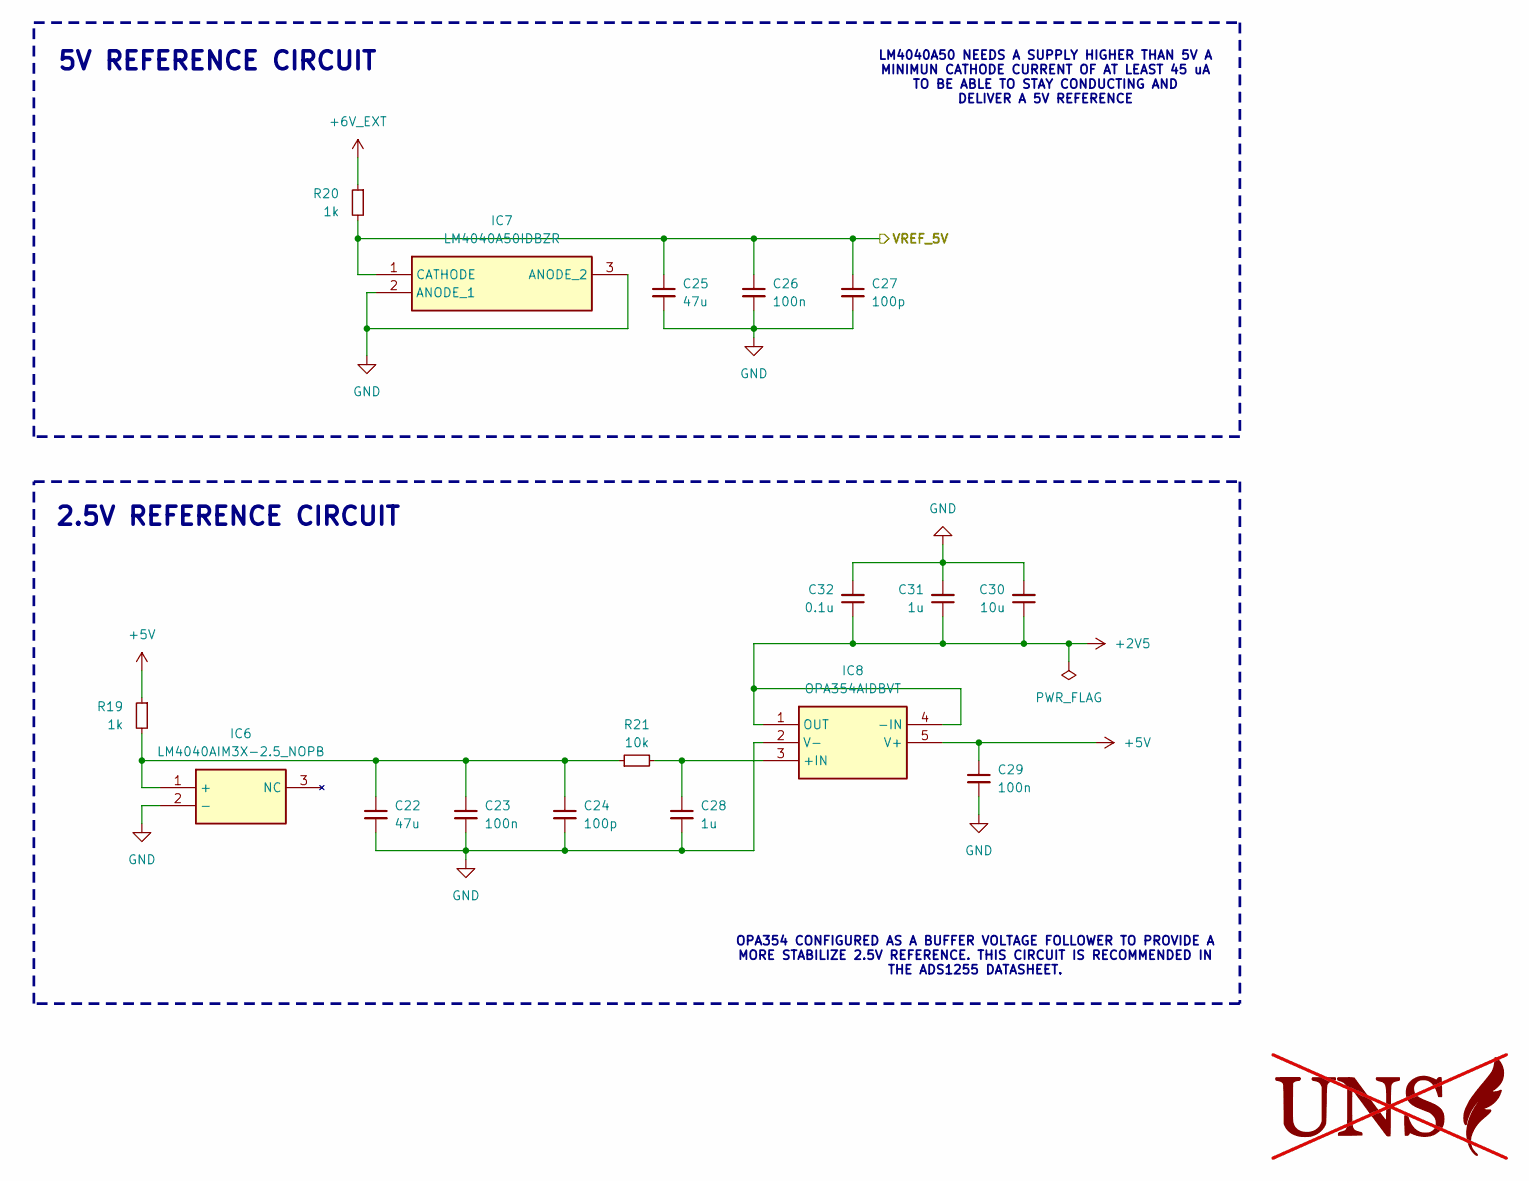
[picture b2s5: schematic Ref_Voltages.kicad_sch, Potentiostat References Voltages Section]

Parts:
C22, C25: 47u; C_0805_2012Metric_Pad1.18x1.45mm_HandSolder
C23, C26, C29: 100n; C_0805_2012Metric_Pad1.18x1.45mm_HandSolder
C24, C27: 100p; C_0805_2012Metric_Pad1.18x1.45mm_HandSolder
C28: 1u; C_1206_3216Metric_Pad1.33x1.80mm_HandSolder
C30: 10u; C_1206_3216Metric_Pad1.33x1.80mm_HandSolder
C31: 1u; C_0805_2012Metric_Pad1.18x1.45mm_HandSolder
C32: 0.1u; C_0805_2012Metric_Pad1.18x1.45mm_HandSolder
IC6: LM4040AIM3X-2.5_NOPB; SOT95P237X112_LM40402_5; MFR.Part # LM4040AIM3X-2.5/NOPB
IC7: LM4040A50IDBZR; SOT95P237X112_LM4040A5; MFR.Part # LM4040A50IDBZR
IC8: OPA354AIDBVT; SOT95P280X145_OPA354; MFR.Part # OPA354AIDBVT
R19, R20: 1k; R_0603_1608Metric_Pad0.98x0.95mm_HandSolder
R21: 10k; R_0603_1608Metric_Pad0.98x0.95mm_HandSolder
U11: not fitted

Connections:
+2V5: C30.1, C31.1, C32.1, IC8.1 (OUT), IC8.4 (-IN); also elsewhere on the board
+5V: C29.1, IC8.5 (V+), R19.1; also elsewhere on the board
+6V_EXT: R20.1; also elsewhere on the board
/REF5V: C25.1, C26.1, C27.1, IC7.1 (CATHODE), R20.2; also elsewhere on the board
GND: C22.2, C23.2, C24.2, C25.2, C26.2, C27.2, C28.2, C29.2, C30.2, C31.2, C32.2, IC6.2 (-), IC7.2 (ANODE_1), IC7.3 (ANODE_2), IC8.2 (V-); also elsewhere on the board
unnamed: C22.1, C23.1, C24.1, IC6.1 (+), R19.2, R21.1
unnamed: C28.1, IC8.3 (+IN), R21.2

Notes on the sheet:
5V REFERENCE CIRCUIT
OPA354 CONFIGURED AS A BUFFER VOLTAGE FOLLOWER TO PROVIDE A MORE STABILIZE 2.5V REFERENCE. THIS CIRCUIT IS RECOMMENDED IN THE ADS1255 DATASHEET.
LM4040A50 NEEDS A SUPPLY HIGHER THAN 5V A MINIMUN CATHODE CURRENT OF AT LEAST 45 uA TO BE ABLE TO STAY CONDUCTING AND DELIVER A 5V REFERENCE
2.5V REFERENCE CIRCUIT

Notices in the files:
Software/ESP32_Firmware/PotentiostatV2_Firmware/components/ADS1255/include/ads1255.h:
Copyright (c) 2020 Simon Burkhardt
README.md:
License: Open Source
